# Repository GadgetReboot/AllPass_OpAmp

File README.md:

# AllPass_OpAmp
<br><br><BR><BR>
Dual op amp all pass filters for breadboarding of phaser effects

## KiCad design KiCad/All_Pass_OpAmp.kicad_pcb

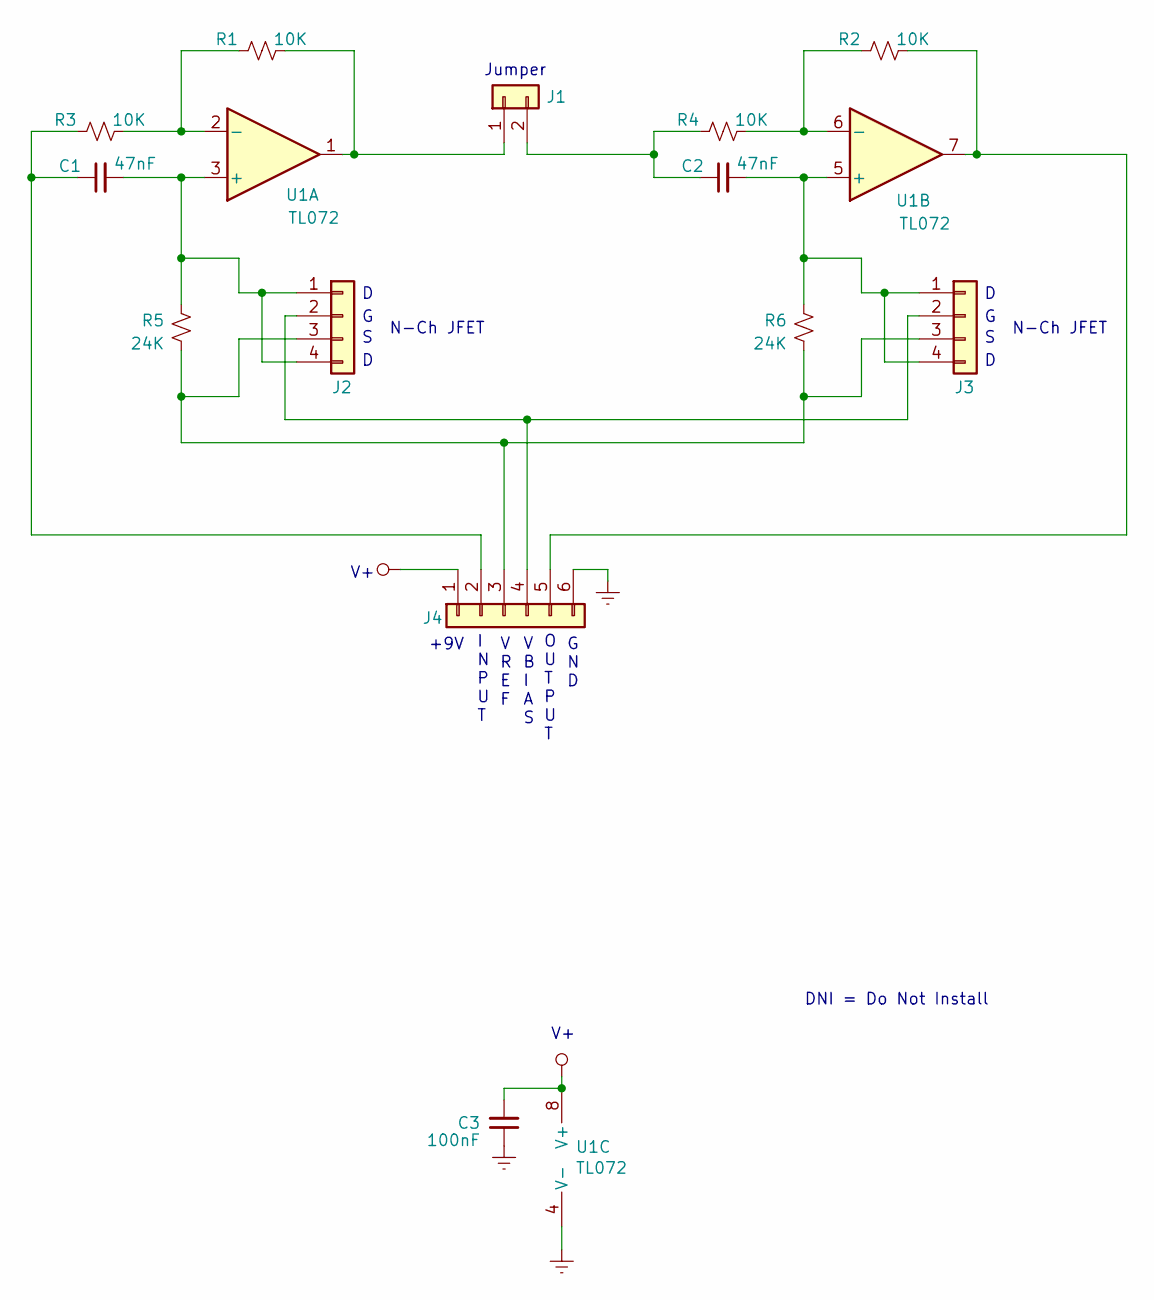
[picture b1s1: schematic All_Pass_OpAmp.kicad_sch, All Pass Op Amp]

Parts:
C1, C2: 47nF; C_Disc_D3.0mm_W1.6mm_P2.50mm
C3: 100nF; C_Disc_D3.0mm_W1.6mm_P2.50mm
J1: Conn_01x02; PinHeader_1x02_P2.54mm_Vertical
J2, J3: Conn_01x04; PinHeader_1x04_P2.54mm_Vertical
J4: Conn_01x06; PinHeader_1x06_P2.54mm_Vertical
R1, R2, R3, R4: 10K; R_Axial_DIN0207_L6.3mm_D2.5mm_P10.16mm_Horizontal
R5, R6: 24K; R_Axial_DIN0207_L6.3mm_D2.5mm_P10.16mm_Horizontal
U1: TL072; DIP-8_W7.62mm

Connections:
GNDREF: C3.1, J4.6, U1.4 (V-)
unnamed: J1.1, R1.1, U1.1
unnamed: C2.1, J1.2, R4.2
unnamed: C1.2, J2.1, J2.4, R5.1, U1.3 (+)
unnamed: J2.2, J3.2, J4.4
unnamed: J2.3, J3.3, J4.3, R5.2, R6.2
unnamed: C2.2, J3.1, J3.4, R6.1, U1.5 (+)
unnamed: C1.1, J4.2, R3.2
unnamed: J4.5, R2.1, U1.7
unnamed: R1.2, R3.1, U1.2 (-)
unnamed: R2.2, R4.1, U1.6 (-)
VCC: C3.2, J4.1, U1.8 (V+)

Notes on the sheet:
Jumper
I N P U T
N-Ch JFET
O U T P U T
G N D
+9V
DNI = Do Not Install
V B I A S
V R E F

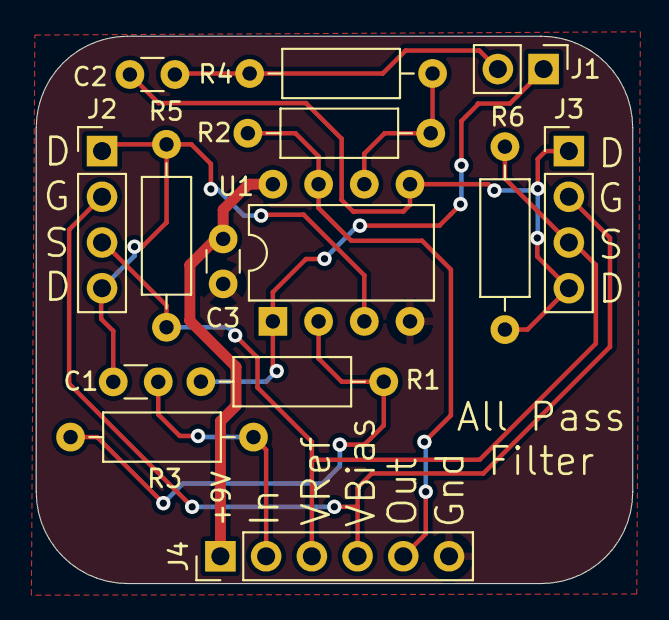
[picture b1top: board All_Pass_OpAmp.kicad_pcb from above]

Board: 2 copper layers, 33.1 x 30.4 mm, 14 parts (0 on the bottom side), 12 nets.
